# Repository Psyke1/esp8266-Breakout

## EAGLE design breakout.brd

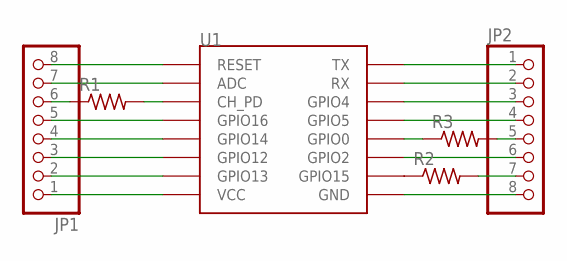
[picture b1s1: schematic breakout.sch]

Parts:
JP1, JP2: PINHD-1X8_2.54; 1X08
R1, R2, R3: R-US_R0805; R0805
U1: ESP12SMD; ESP12-SMD

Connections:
unnamed: JP1.1, U1.VCC
unnamed: JP1.2, U1.GPIO13
unnamed: JP1.3, U1.GPIO12
unnamed: JP1.4, U1.GPIO14
unnamed: JP1.5, U1.GPIO16
unnamed: JP1.7, U1.ADC
unnamed: JP1.8, U1.RESET
unnamed: JP2.1, U1.TXD0 (TX)
unnamed: JP2.2, U1.RXD0 (RX)
unnamed: JP2.3, U1.GPIO4
unnamed: JP2.4, U1.GPIO5
unnamed: R3.1, U1.GPIO0
unnamed: JP2.6, U1.GPIO2
unnamed: JP1.6, R1.1
unnamed: JP2.8, U1.GND
unnamed: R1.2, U1.CH_PD
unnamed: R2.1, U1.GPIO15
unnamed: JP2.5, R3.2
unnamed: JP2.7, R2.2

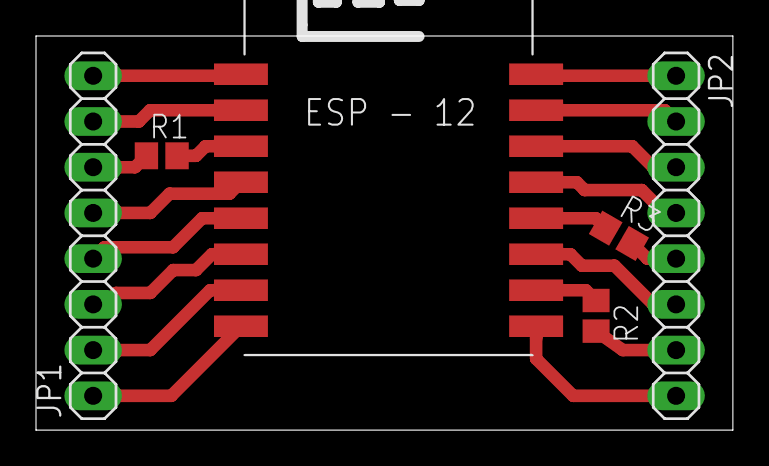
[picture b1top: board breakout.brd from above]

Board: 2 copper layers, 38.7 x 21.9 mm, 6 parts (0 on the bottom side), 19 nets.

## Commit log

2018-11-21 Add files via upload
    Initial commit
2018-11-22 Added GPIO0 resistor
2018-11-23 Modified pads, changed traces width and gcode options
